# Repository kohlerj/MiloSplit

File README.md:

# MiloSplit

Milo Junction Box PCB Splitter.

Gather all electrical signal to the back of the Milo so that only one umbilical goes to the CASA electrical cabinet.

See details on Printables: [link](https://www.printables.com/model/1209545-milosplit-a-milo-v15-junction-box)

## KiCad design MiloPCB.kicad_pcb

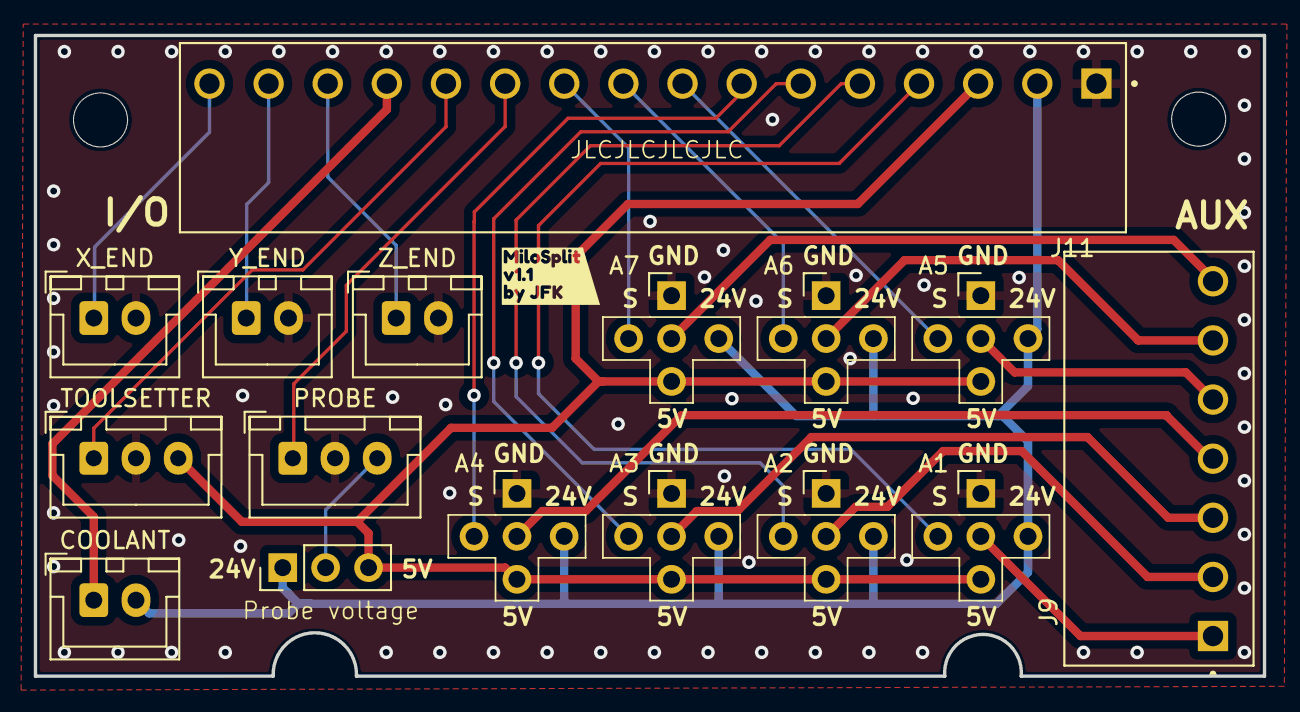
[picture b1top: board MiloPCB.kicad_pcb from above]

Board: 2 copper layers, 72.8 x 37.9 mm, 19 parts (0 on the bottom side), 24 nets.

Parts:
A1, A2, A3, A4, A5, A6, A7: Jumper_5_Open; CustomJumper_5
COOLANT: Coolant; JST_XH_B2B-XH-A_1x02_P2.50mm_Vertical
H1, H2: MountingHole; MountingHole_3.2mm_M3
J9: Additional; PHOENIX_1989007
J11: 1989094; PHOENIX_1989094
JP8: Jumper_3_Open; PinHeader_1x03_P2.54mm_Vertical
PROBE: Probe; JST_XH_B3B-XH-A_1x03_P2.50mm_Vertical
TOOLSETTER: Toolsetter; JST_XH_B3B-XH-A_1x03_P2.50mm_Vertical
X_END: Xmotor_endstop; JST_XH_B2B-XH-A_1x02_P2.50mm_Vertical
Y_END: Y_Endstop; JST_XH_B2B-XH-A_1x02_P2.50mm_Vertical
Z_END: Zmotor_endstop; JST_XH_B2B-XH-A_1x02_P2.50mm_Vertical
kibuzzard-67C050AC: G***; kibuzzard-67C050AC

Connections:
+5V: A1.3 (B), A2.3 (B), A3.3 (B), A4.3 (B), A5.3 (B), A6.3 (B), A7.3 (B), J11.3, JP8.3 (B), TOOLSETTER.3
+24V: A1.5 (D), A2.5 (D), A3.5 (D), A4.5 (D), A5.5 (D), A6.5 (D), A7.5 (D), COOLANT.2, J11.2, JP8.1 (A)
/Coolant: COOLANT.1, J11.13
/Probe: J11.11, PROBE.1
/Toolsetter: J11.12, TOOLSETTER.1
/Xendstop: J11.16, X_END.1
/Yendstop: J11.15, Y_END.1
/Zendstop: J11.14, Z_END.1
GND: A1.2 (A), A2.2 (A), A3.2 (A), A4.2 (A), A5.2 (A), A6.2 (A), A7.2 (A), J11.1, PROBE.2, TOOLSETTER.2, X_END.2, Y_END.2, Z_END.2
unnamed: JP8.2 (C), PROBE.3
unnamed: A1.4 (C), J11.4
unnamed: A1.1 (IN), J9.1
unnamed: A2.4 (C), J11.5
unnamed: A2.1 (IN), J9.2
unnamed: A3.4 (C), J11.6
unnamed: A3.1 (IN), J9.3
unnamed: A4.4 (C), J11.7
unnamed: A4.1 (IN), J9.4
unnamed: A5.4 (C), J11.8
unnamed: A5.1 (IN), J9.5
unnamed: A6.4 (C), J11.9
unnamed: A6.1 (IN), J9.6
unnamed: A7.4 (C), J11.10
unnamed: A7.1 (IN), J9.7

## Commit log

2025-02-27 First commit ;)
2025-02-27 Add license
2025-02-27 Add README
2025-02-27 Relink 3D models
2025-02-27 Add render
2025-02-27 Update link and render
